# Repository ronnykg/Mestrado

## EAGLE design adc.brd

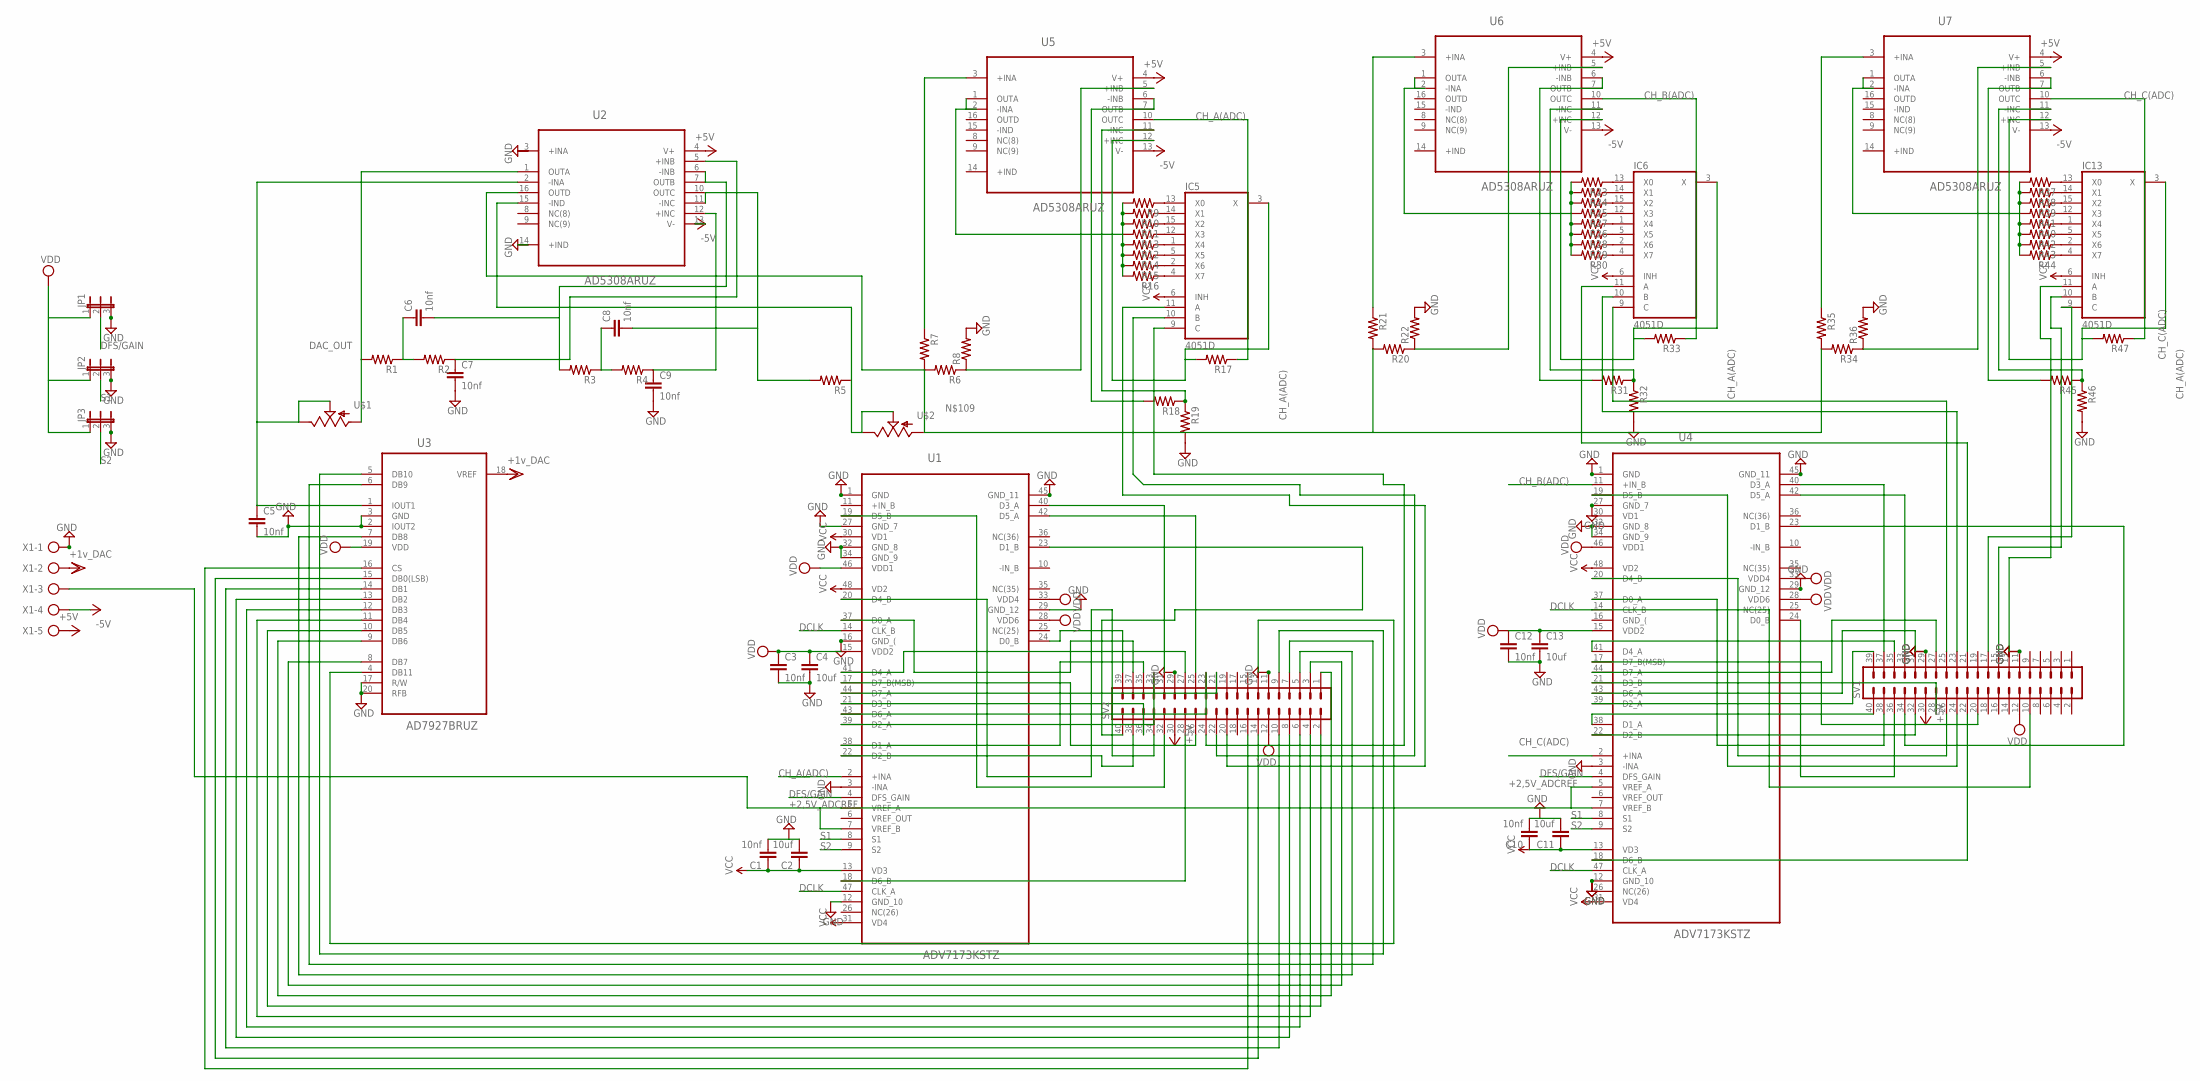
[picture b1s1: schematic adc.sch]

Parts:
C1, C3, C5, C6, C7, C8, C9, C10, C12: 10nf; C0603
C2, C4, C11, C13: 10uf; C0603
IC5, IC6, IC13: 4051D; SO16
JP1, JP2, JP3: JP2E; JP2
R1, R2, R3, R4, R5, R6, R7, R8, R9, R10, R11, R12, R13, R14, R15, R16, R17, R18, R19, R20, R21, R22, R23, R24, R25, R26, R27, R28, R29, R30, R31, R32, R33, R34, R35, R36, R37, R38, R39, R40, R41, R42, R43, R44, R45, R46, R47: RESISTOR0603; 0603
SV1, SV2: MA20-2
U1, U4: ADV7173KSTZ; QFP50P900X900X160-48N
U2, U5, U6, U7: AD5308ARUZ; SOP65P640X120-16N
U3: AD7927BRUZ; SOP65P640X120-20N
U$1, U$2: POT100K_3362U; 3362U
X1: AK300/5

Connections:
+2,5V_ADCREF: U1.5 (VREF_A), U1.7 (VREF_B), U4.5 (VREF_A), U4.7 (VREF_B), X1.3
+5V: SV1.30, SV2.30, U2.4 (V+), U5.4 (V+), U6.4 (V+), U7.4 (V+), X1.5
+INA: U2.3 (+INA)
+IN_B: U1.11 (+IN_B)
-5V: U2.13 (V-), U5.13 (V-), U6.13 (V-), U7.13 (V-), X1.4
CH_A(ADC): R17.1, U1.2 (+INA), U5.10 (OUTC)
CH_B(ADC): R33.1, U4.11 (+IN_B), U6.10 (OUTC)
CH_C(ADC): R47.1, U4.2 (+INA), U7.10 (OUTC)
DAC_OUT: R1.2, U2.1 (OUTA), U$1.P$3 (A)
DCLK: SV1.10, U1.14 (CLK_B), U1.47 (CLK_A), U4.14 (CLK_B), U4.47 (CLK_A)
DFS/GAIN: JP1.2, U1.4 (DFS_GAIN), U4.4 (DFS_GAIN)
GND: C1.2, C2.2, C3.2, C4.2, C5.2, C7.2, C9.2, C10.2, C11.2, C12.2, C13.2, IC5.8 (GND), IC6.8 (GND), IC13.8 (GND), JP1.3, JP2.3, JP3.3, R8.2, R19.2, R22.2, R32.2, R36.2, R46.2, SV1.11, SV1.29, SV2.11, SV2.29, U1.1 (GND), U1.3 (-INA), U1.12 (GND_10), U1.16 (GND_(), U1.27 (GND_7), U1.29 (GND_12), U1.32 (GND_8), U1.34 (GND_9), U1.45 (GND_11), U2.14 (+IND), U3.2 (IOUT2), U3.3 (GND), U3.17 (R/W), U3.20 (RFB), U4.1 (GND), U4.3 (-INA), U4.12 (GND_10), U4.27 (GND_7), U4.29 (GND_12), U4.32 (GND_8), U4.34 (GND_9), U4.45 (GND_11), X1.1
unnamed: C7.1, R2.1, U2.5 (+INB)
unnamed: C6.1, R1.1, R2.2
unnamed: C5.1, U2.2 (-INA), U3.1 (IOUT1), U$1.P$1 (E), U$1.P$2 (S)
unnamed: C6.2, R3.2, U2.6 (-INB), U2.7 (OUTB)
unnamed: C9.1, R4.1, U2.12 (+INC)
unnamed: C8.1, R3.1, R4.2
unnamed: C8.2, R5.2, U2.10 (OUTC), U2.11 (-INC)
unnamed: R5.1, U2.15 (-IND), U$2.P$1 (E), U$2.P$2 (S)
unnamed: SV2.31, U1.40 (D3_A)
unnamed: SV2.25, U1.42 (D5_A)
unnamed: SV2.39, U1.24 (D0_B)
unnamed: SV2.32, U1.19 (D5_B)
unnamed: SV2.34, U1.20 (D4_B)
unnamed: SV2.37, U1.37 (D0_A)
unnamed: SV2.27, U1.41 (D4_A)
unnamed: SV2.21, U1.44 (D7_A)
unnamed: SV2.36, U1.21 (D3_B)
unnamed: SV2.23, U1.43 (D6_A)
unnamed: SV2.33, U1.39 (D2_A)
unnamed: SV2.35, U1.38 (D1_A)
unnamed: SV2.38, U1.22 (D2_B)
unnamed: SV2.28, U1.18 (D6_B)
unnamed: SV2.26, U1.17 (D7_B(MSB))
unnamed: SV2.13, U3.4 (DB11)
unnamed: SV2.40, U1.23 (D1_B)
unnamed: SV2.9, U3.5 (DB10)
unnamed: SV2.7, U3.6 (DB9)
unnamed: SV2.5, U3.7 (DB8)
unnamed: SV2.3, U3.8 (DB7)
unnamed: SV2.1, U3.9 (DB6)
unnamed: SV2.2, U3.10 (DB5)
unnamed: SV2.4, U3.11 (DB4)
unnamed: SV2.6, U3.12 (DB3)
unnamed: SV2.8, U3.13 (DB2)
unnamed: SV2.10, U3.14 (DB1)
unnamed: SV2.14, U3.15 (DB0(LSB))
unnamed: SV1.38, U4.37 (D0_A)
unnamed: IC5.13 (X0), R9.1
unnamed: IC5.14 (X1), R10.1
unnamed: IC5.15 (X2), R11.1
unnamed: IC5.1 (X4), R12.1
unnamed: IC5.12 (X3), R13.1
unnamed: IC5.5 (X5), R14.1
unnamed: IC5.2 (X6), R15.1
unnamed: IC5.4 (X7), R16.1
unnamed: IC6.13 (X0), R23.1
unnamed: IC6.14 (X1), R24.1
unnamed: R23.2, R24.2, R25.2, R26.2, R27.2, R28.2, R29.2, R30.2
unnamed: R9.2, R10.2, R11.2, R12.2, R13.2, R14.2, R15.2, R16.2
unnamed: R18.1, R19.1, U5.11 (-INC)
unnamed: IC5.3 (X), R17.2, U5.12 (+INC)
unnamed: IC6.15 (X2), R25.1
unnamed: IC6.1 (X4), R26.1
unnamed: IC6.12 (X3), R27.1
unnamed: IC6.5 (X5), R28.1
unnamed: IC6.2 (X6), R29.1
unnamed: IC6.4 (X7), R30.1
unnamed: R31.2, U6.6 (-INB), U6.7 (OUTB)
unnamed: R45.2, U7.6 (-INB), U7.7 (OUTB)
unnamed: IC13.3 (X), R47.2, U7.12 (+INC)
unnamed: IC6.3 (X), R33.2, U6.12 (+INC)
unnamed: IC13.13 (X0), R37.1
unnamed: IC13.14 (X1), R38.1
unnamed: IC13.15 (X2), R39.1
unnamed: IC13.1 (X4), R40.1
unnamed: IC13.12 (X3), R41.1
unnamed: IC13.5 (X5), R42.1
unnamed: IC13.2 (X6), R43.1
unnamed: IC13.4 (X7), R44.1
unnamed: R34.1, R36.1, U7.5 (+INB)
unnamed: R6.1, R8.1, U5.5 (+INB)
unnamed: R20.1, R22.1, U6.5 (+INB)
unnamed: R7.1, U5.3 (+INA)
unnamed: SV1.40, U4.38 (D1_A)
unnamed: SV1.39, U4.39 (D2_A)
unnamed: SV1.36, U4.24 (D0_B)
unnamed: SV1.24, U4.19 (D5_B)
unnamed: SV1.26, U4.20 (D4_B)
unnamed: SV1.37, U4.40 (D3_A)
unnamed: SV1.35, U4.41 (D4_A)
unnamed: SV1.33, U4.42 (D5_A)
unnamed: SV1.28, U4.21 (D3_B)
unnamed: SV1.31, U4.43 (D6_A)
unnamed: SV1.27, U4.44 (D7_A)
unnamed: SV1.32, U4.22 (D2_B)
unnamed: SV1.22, U4.18 (D6_B)
unnamed: SV1.20, U4.17 (D7_B(MSB))
unnamed: SV1.34, U4.23 (D1_B)
unnamed: IC5.9 (C), SV2.24
unnamed: IC5.10 (B), SV2.22
unnamed: IC13.9 (C), SV1.17
unnamed: IC13.10 (B), SV1.15
unnamed: IC13.11 (A), SV1.13
unnamed: IC6.9 (C), SV1.25
unnamed: IC6.10 (B), SV1.23
unnamed: IC6.11 (A), SV1.21
unnamed: R18.2, U5.6 (-INB), U5.7 (OUTB)
unnamed: U5.1 (OUTA), U5.2 (-INA)
unnamed: R31.1, R32.1, U6.11 (-INC)
unnamed: R37.2, R38.2, R39.2, R40.2, R41.2, R42.2, R43.2, R44.2
unnamed: U6.1 (OUTA), U6.2 (-INA)
unnamed: R45.1, R46.1, U7.11 (-INC)
unnamed: U7.1 (OUTA), U7.2 (-INA)
unnamed: R35.1, U7.3 (+INA)
unnamed: R21.1, U6.3 (+INA)
unnamed: R6.2, R7.2, R20.2, R21.2, R34.2, R35.2, U2.16 (OUTD), U$2.P$3 (A)
unnamed: IC5.11 (A), SV2.20
unnamed: SV2.16, U3.16 (CS)
S1: JP2.2, U1.8 (S1), U4.8 (S1)
S2: JP3.2, U1.9 (S2), U4.9 (S2)
VCC: C1.1, C2.1, C10.1, C11.1, IC5.6 (INH), IC5.16 (VCC), IC6.6 (INH), IC6.16 (VCC), IC13.6 (INH), IC13.16 (VCC), U1.13 (VD3), U1.30 (VD1), U1.31 (VD4), U1.48 (VD2), U4.13 (VD3), U4.31 (VD4), U4.48 (VD2)
VD1: U4.30 (VD1)
VDD: C3.1, C4.1, C12.1, C13.1, JP1.1, JP2.1, JP3.1, SV1.12, SV2.12, U1.15 (VDD2), U1.28 (VDD6), U1.33 (VDD4), U1.46 (VDD1), U3.18 (VREF), U3.19 (VDD), U4.15 (VDD2), U4.28 (VDD6), U4.33 (VDD4), U4.46 (VDD1), X1.2
VEE: IC5.7 (VEE), IC6.7 (VEE), IC13.7 (VEE)

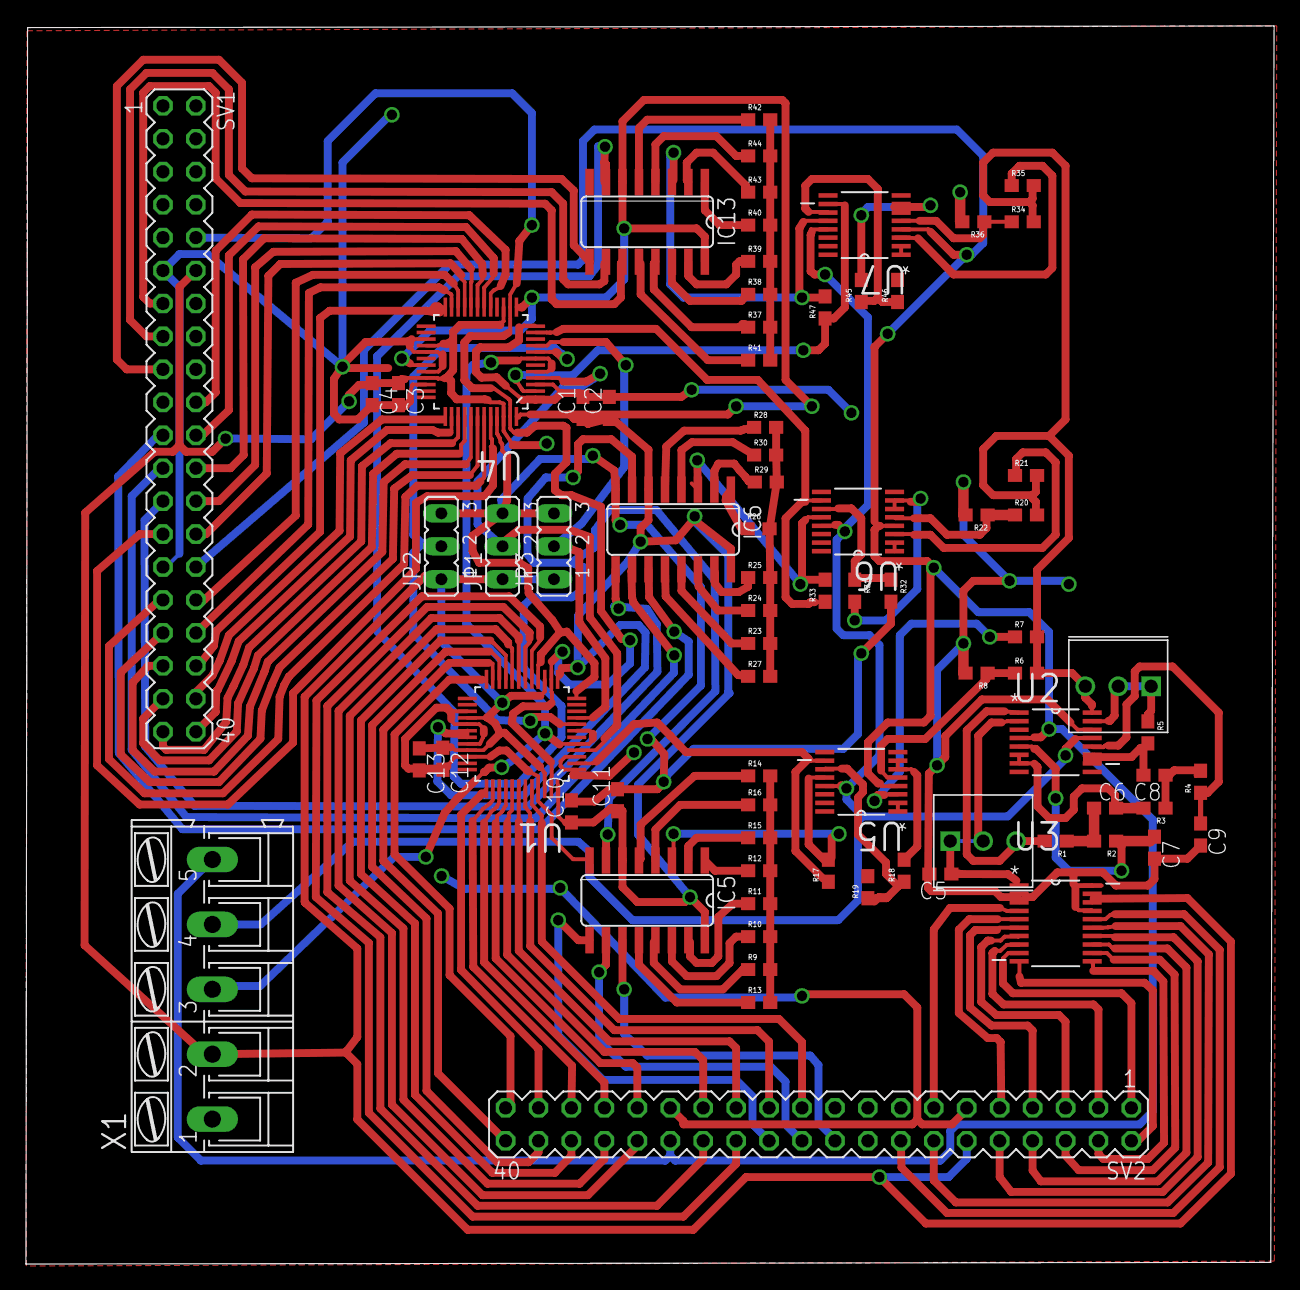
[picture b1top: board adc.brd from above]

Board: 2 copper layers, 96.2 x 95.5 mm, 78 parts (0 on the bottom side), 123 nets.

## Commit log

2015-01-12 :lollipop: Added .gitattributes & .gitignore files
2015-01-12 Add files
2015-01-12 deleted files
2015-01-12 deleted file
2015-01-12 Calendário prévio
2015-01-13 Inicio do projeto final
2015-01-15 atualizado diabetes/neuro
2015-01-21 Instrumentação
2015-01-27 placa ADC v1
2015-02-10 VHDL
2015-03-12 autalização
2015-04-15 atualização
    calculando mais de 1 freq no vhdl. C# com recebimento e tratamento
    simpres (com erros) dos dados.
2015-05-26 Atualização
    VHDL com SWITCH CASE. 1-16 start end package
    C# com controle de erro
    ADC com alterações
2015-05-28 ADC update
    Atualizado algumas trilhas e GND não conectado
2015-06-10 Up to date
    atualização do projeto .doc
